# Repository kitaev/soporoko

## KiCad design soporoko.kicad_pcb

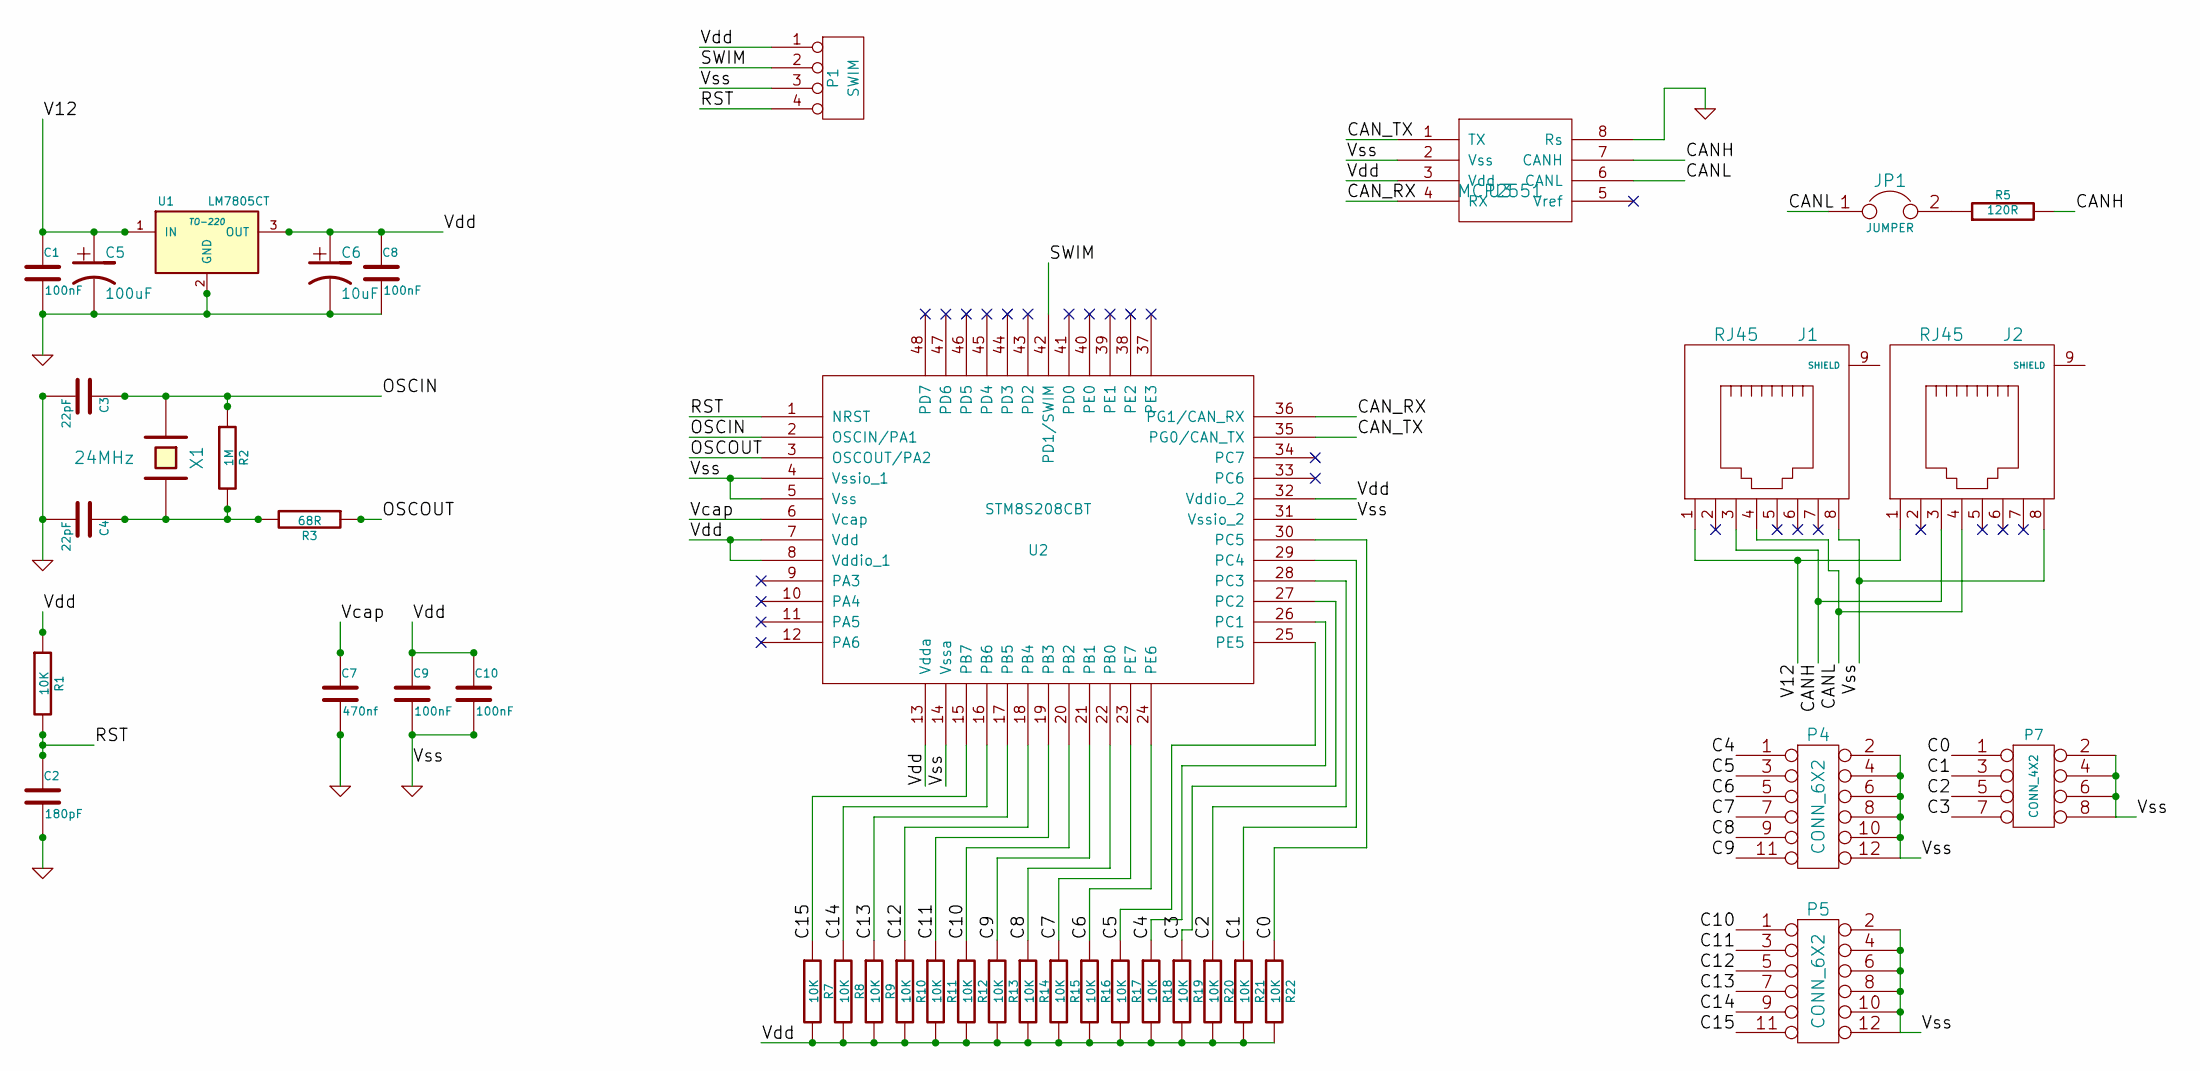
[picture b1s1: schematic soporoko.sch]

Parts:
C1, C8, C9, C10: 100nF
C2: 180pF
C3, C4: 22pF
C5: 100uF
C6: 10uF
C7: 470nf
J1, J2: RJ45
JP1: JUMPER
P1: SWIM
P4, P5: CONN_6X2
P7: CONN_4X2
R1, R7, R8, R9, R10, R11, R12, R13, R14, R15, R16, R17, R18, R19, R20, R21, R22: 10K
R2: 1M
R3: 68R
R5: 120R
U1: LM7805CT; TO-220
U2: STM8S208CBT; MODULE
U3: MCP2551
X1: 24MHz

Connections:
/C0: P7.1, R22.1, U2.30 (PC5)
/C1: P7.3, R21.1, U2.29 (PC4)
/C2: P7.5, R20.1, U2.28 (PC3)
/C3: P7.7, R19.1, U2.27 (PC2)
/C4: P4.1, R18.1, U2.26 (PC1)
/C5: P4.3, R17.1, U2.25 (PE5)
/C6: P4.5, R16.1, U2.24 (PE6)
/C7: P4.7, R15.1, U2.23 (PE7)
/C8: P4.9, R14.1, U2.22 (PB0)
/C9: P4.11, R13.1, U2.21 (PB1)
/C10: P5.1, R12.1, U2.20 (PB2)
/C11: P5.3, R11.1, U2.19 (PB3)
/C12: P5.5, R10.1, U2.18 (PB4)
/C13: P5.7, R9.1, U2.17 (PB5)
/C14: P5.9, R8.1, U2.16 (PB6)
/C15: P5.11, R7.1, U2.15 (PB7)
/CANH: J1.3, J2.3, R5.2, U3.7 (CANH)
/CANL: J1.4, J2.4, JP1.1, U3.6 (CANL)
/CAN_RX: U2.36 (PG1/CAN_RX), U3.4 (RX)
/CAN_TX: U2.35 (PG0/CAN_TX), U3.1 (TX)
/OSCIN: C3.1, R2.1, U2.2 (OSCIN/PA1), X1.1
/OSCOUT: R3.1, U2.3 (OSCOUT/PA2)
/RST: C2.1, P1.4, R1.2, U2.1 (NRST)
/SWIM: P1.2, U2.42 (PD1/SWIM)
/V12: C1.1, C5.1, J1.1, J2.1, U1.1 (IN)
/Vcap: C7.1, U2.6 (Vcap)
/Vdd: C6.1, C8.1, C9.1, C10.1, P1.1, R1.1, R7.2, R8.2, R9.2, R10.2, R11.2, R12.2, R13.2, R14.2, R15.2, R16.2, R17.2, R18.2, R19.2, R20.2, R21.2, R22.2, U1.3 (OUT), U2.7 (Vdd), U2.8 (Vddio_1), U2.13 (Vdda), U2.32 (Vddio_2), U3.3 (Vdd)
GND: C1.2, C2.2, C3.2, C4.2, C5.2, C6.2, C7.2, C8.2, C9.2, C10.2, J1.8, J2.8, P1.3, P4.2, P4.4, P4.6, P4.8, P4.10, P4.12, P5.2, P5.4, P5.6, P5.8, P5.10, P5.12, P7.2, P7.4, P7.6, P7.8, U1.2 (GND), U2.4 (Vssio_1), U2.5 (Vss), U2.14 (Vssa), U2.31 (Vssio_2), U3.2 (Vss), U3.8 (Rs)
unnamed: C4.1, R2.2, R3.2, X1.2
unnamed: JP1.2, R5.1

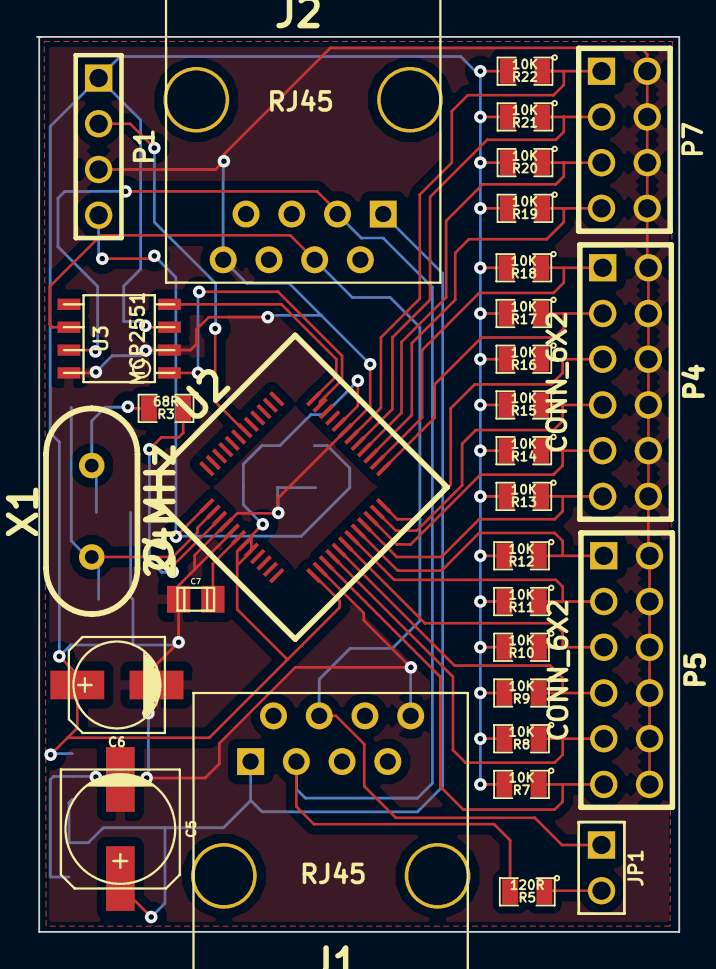
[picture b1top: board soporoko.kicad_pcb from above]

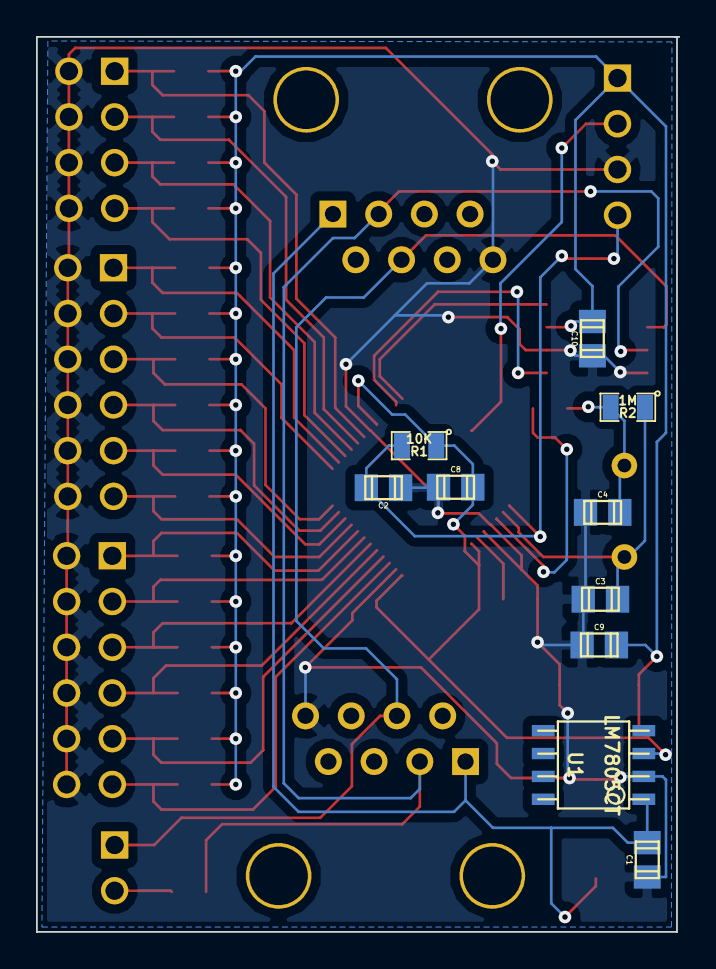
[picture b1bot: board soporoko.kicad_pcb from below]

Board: 2 copper layers, 35.7 x 49.7 mm, 41 parts (10 on the bottom side), 30 nets.

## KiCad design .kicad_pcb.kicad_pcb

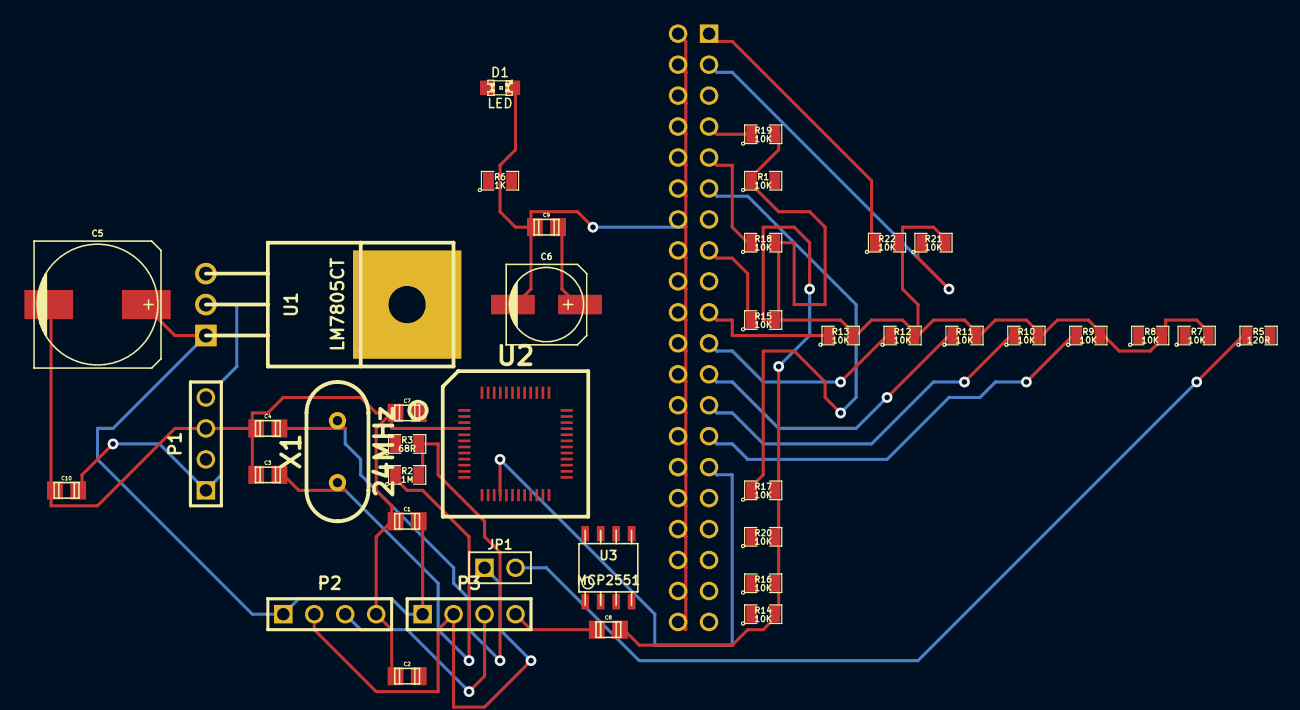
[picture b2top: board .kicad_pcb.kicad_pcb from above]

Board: 2 copper layers, 41 parts (1 on the bottom side), 35 nets.

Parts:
C1, C8, C9, C10: 100nF; c_0805
C2: 180pF; c_0805
C3, C4: 22pF; c_0805
C5: 100uF; c_elec_10x10
C6: 10uF; c_elec_6.3x5.3
C7: 470nf; c_0805
D1: LED; LED-0805
JP1: JUMPER; PIN_ARRAY_2X1
P1: SWIM; PIN_ARRAY_4x1
P2, P3: CAN; PIN_ARRAY_4x1
P4: CONN_20X2; PIN_ARRAY_20X2
R1, R7, R8, R9, R10, R11, R12, R13, R14, R15, R16, R17, R18, R19, R20, R21, R22: 10K; SM0805
R2: 1M; SM0805
R3: 68R; SM0805
R5: 120R; SM0805
R6: 1K; SM0805
U1: LM7805CT; TO220
U2: STM8S208CBT; lqfp48
U3: MCP2551; so-8
X1: 24MHz; HC-49V

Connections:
/C0: P4.1, R22.1, U2.30
/C1: P4.3, R21.1, U2.29
/C2: P4.5, R20.1, U2.28
/C3: P4.7, R19.1, U2.27
/C4: P4.9, R18.1, U2.26
/C5: P4.11, R17.1, U2.25
/C6: P4.13, R16.1, U2.24
/C7: P4.15, R15.1, U2.23
/C8: P4.17, R14.1, U2.22
/C9: P4.19, R13.1, U2.21
/C10: P4.21, R12.1, U2.20
/C11: P4.23, R11.1, U2.19
/C12: P4.25, R10.1, U2.18
/C13: P4.27, R9.1, U2.17
/C14: P4.29, R8.1, U2.16
/C15: P4.31, R7.1, U2.15
/CANH: P2.3, P3.3, R5.2, U3.7
/CANL: JP1.1, P2.2, P3.2, U3.6
/CAN_RX: U2.36, U3.4
/CAN_TX: U2.35, U3.1
/OSCIN: C3.1, R2.1, U2.2, X1.1
/OSCOUT: R3.1, U2.3
/OUT0: P4.33, U2.44
/OUT1: P4.35, U2.45
/OUT2: P4.37, U2.46
/OUT3: P4.39, U2.47
/OUT4: R6.1, U2.48
/RST: C2.1, P1.4, R1.2, U2.1
/SWIM: P1.2, U2.42
/V12: C1.1, C5.1, P2.1, P3.1, U1.1
/Vcap: C7.1, U2.6
/Vdd: C6.1, C8.1, C9.1, C10.1, P1.1, R1.1, R7.2, R8.2, R9.2, R10.2, R11.2, R12.2, R13.2, R14.2, R15.2, R16.2, R17.2, R18.2, R19.2, R20.2, R21.2, R22.2, U1.3, U2.7, U2.8, U2.13, U2.32, U3.3
GND: C1.2, C2.2, C3.2, C4.2, C5.2, C6.2, C7.2, C8.2, C9.2, C10.2, D1.2, P1.3, P2.4, P3.4, P4.2, P4.4, P4.6, P4.8, P4.10, P4.12, P4.14, P4.16, P4.18, P4.20, P4.22, P4.24, P4.26, P4.28, P4.30, P4.32, P4.34, P4.36, P4.38, P4.40, U2.4, U2.5, U2.14, U2.31, U3.2, U3.8
unnamed: C4.1, R2.2, R3.2, X1.2
unnamed: JP1.2, R5.1

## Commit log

2013-06-04 initial
2013-06-16 WIP: PCB
